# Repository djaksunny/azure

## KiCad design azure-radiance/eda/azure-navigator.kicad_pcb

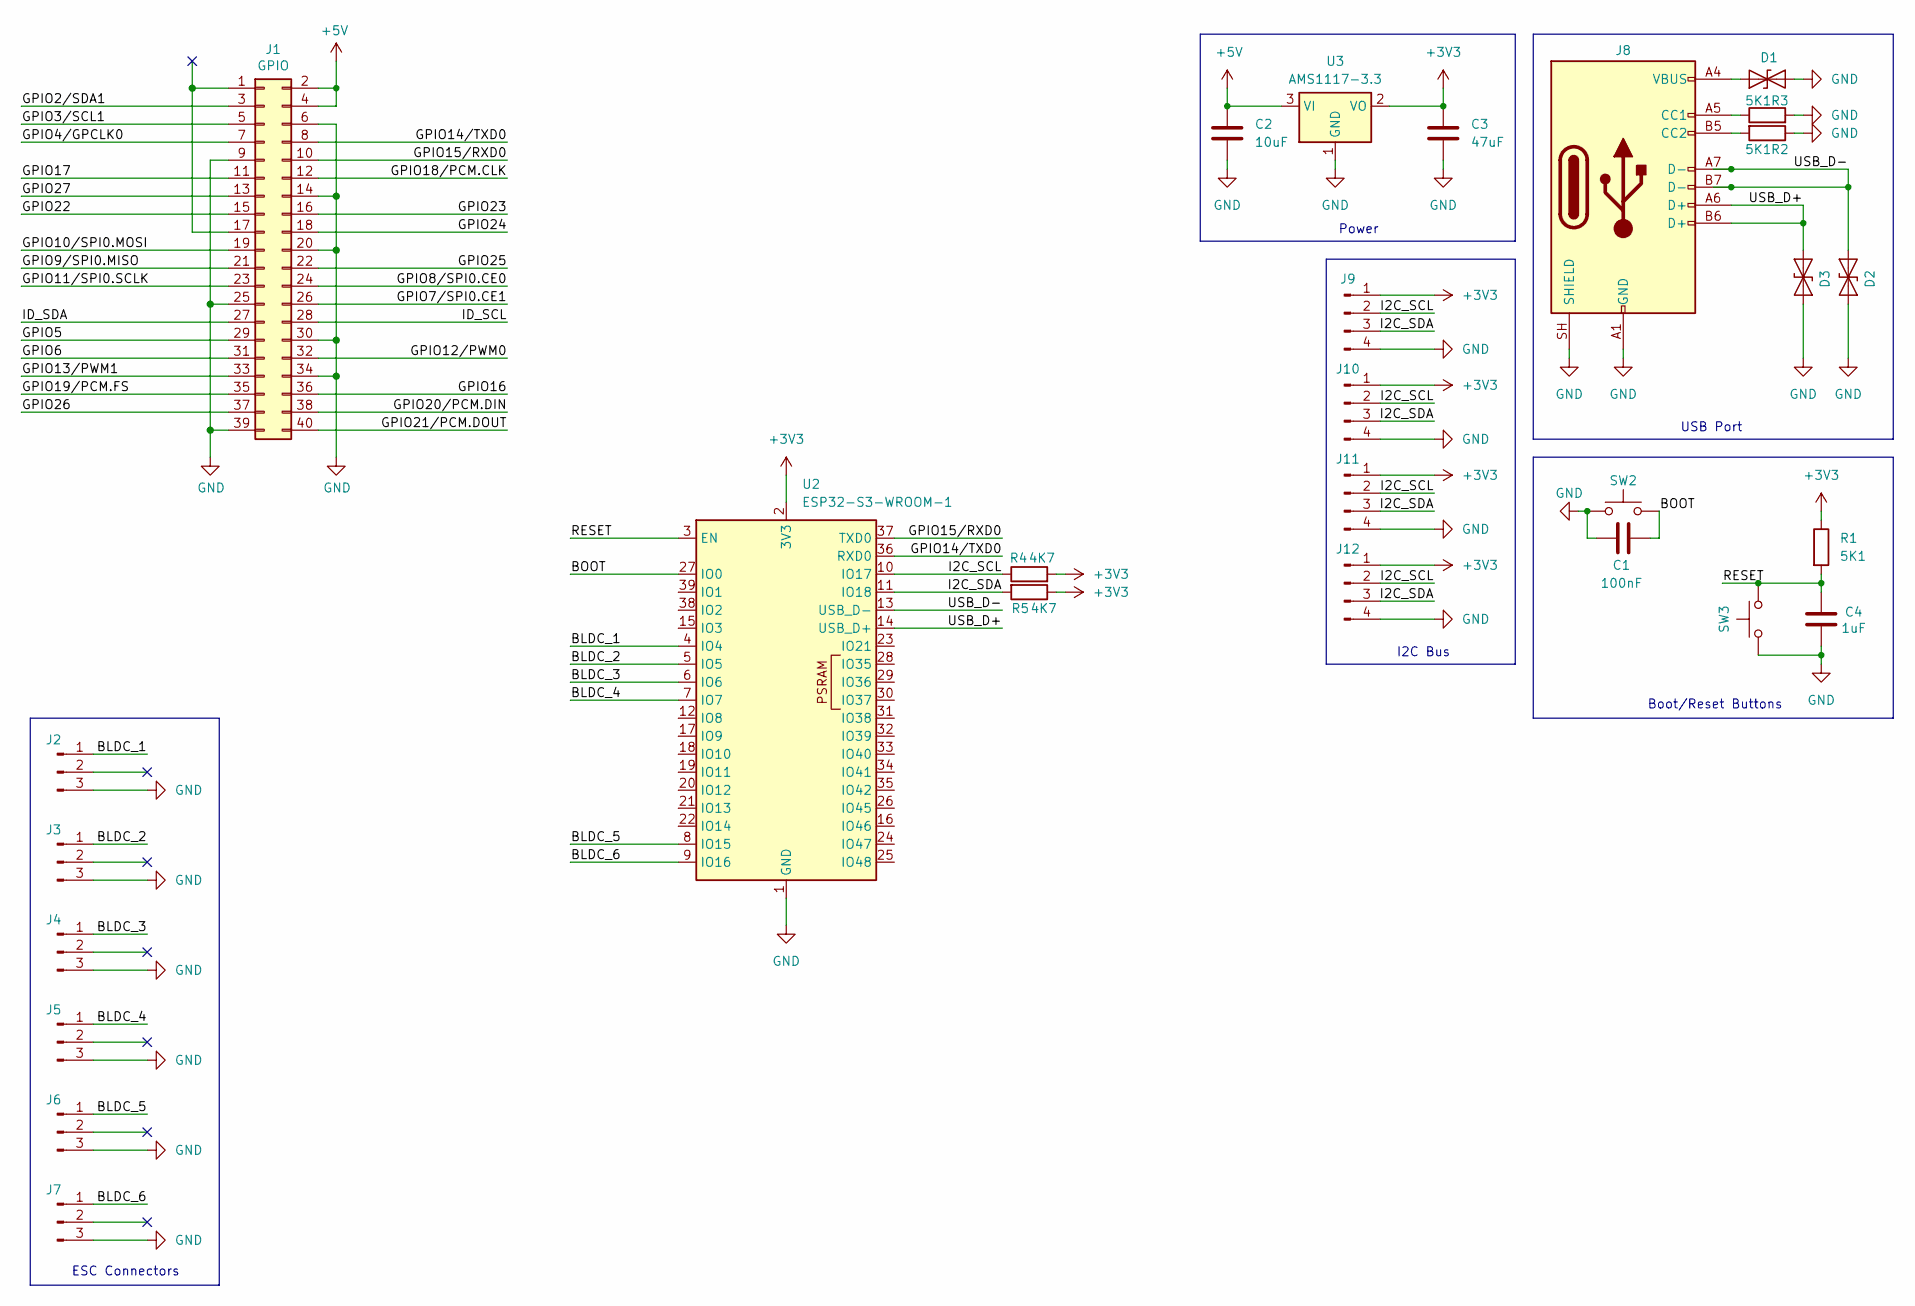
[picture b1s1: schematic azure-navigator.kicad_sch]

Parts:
C1: 100nF; C_1206_3216Metric
C2: 10uF; C_1206_3216Metric
C3: 47uF; C_1206_3216Metric
C4: 1uF; C_1206_3216Metric
D1, D3: ESD9B5.0ST5G; D_1206_3216Metric
D2: ESD9B5.0ST5G; D_SOD-923
J1: GPIO; PinSocket_2x20_P2.54mm_Vertical
J2, J3, J4, J5, J6, J7: Conn_01x03_Pin; JST_XH_B3B-XH-AM_1x03_P2.50mm_Vertical
J8: USB_C_Receptacle_USB2.0_14P; USB_C_Receptacle_Amphenol_124019772112A
J9, J10, J11, J12: Conn_01x04_Pin; JST_PH_B4B-PH-SM4-TB_1x04-1MP_P2.00mm_Vertical
R1, R2, R3: 5K1; R_1206_3216Metric
R4, R5: 4K7; R_1206_3216Metric
SW2, SW3: SW_Push; SW_SPST_PTS810
U2: ESP32-S3-WROOM-1
U3: AMS1117-3.3; SOT-223-3_TabPin2

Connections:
+3V3: C3.1, J9.1, J10.1, J11.1, J12.1, R1.1, R4.2, R5.1, U2.2 (3V3), U3.2 (VO)
+5V: C2.2, J1.2, J1.4, U3.3 (VI)
/BLDC_1: J2.1, U2.4 (IO4)
/BLDC_2: J3.1, U2.5 (IO5)
/BLDC_3: J4.1, U2.6 (IO6)
/BLDC_4: J5.1, U2.7 (IO7)
/BLDC_5: J6.1, U2.8 (IO15)
/BLDC_6: J7.1, U2.9 (IO16)
/BOOT: C1.1, SW2.2, U2.27 (IO0)
/GPIO2/SDA1: J1.3
/GPIO3/SCL1: J1.5
/GPIO4/GPCLK0: J1.7
/GPIO5: J1.29
/GPIO6: J1.31
/GPIO7/SPI0.CE1: J1.26
/GPIO8/SPI0.CE0: J1.24
/GPIO9/SPI0.MISO: J1.21
/GPIO10/SPI0.MOSI: J1.19
/GPIO11/SPI0.SCLK: J1.23
/GPIO12/PWM0: J1.32
/GPIO13/PWM1: J1.33
/GPIO14/TXD0: J1.8, U2.36 (RXD0)
/GPIO15/RXD0: J1.10, U2.37 (TXD0)
/GPIO16: J1.36
/GPIO17: J1.11
/GPIO18/PCM.CLK: J1.12
/GPIO19/PCM.FS: J1.35
/GPIO20/PCM.DIN: J1.38
/GPIO21/PCM.DOUT: J1.40
/GPIO22: J1.15
/GPIO23: J1.16
/GPIO24: J1.18
/GPIO25: J1.22
/GPIO26: J1.37
/GPIO27: J1.13
/I2C_SCL: J9.2, J10.2, J11.2, J12.2, R4.1, U2.10 (IO17)
/I2C_SDA: J9.3, J10.3, J11.3, J12.3, R5.2, U2.11 (IO18)
/ID_SCL: J1.28
/ID_SDA: J1.27
/RESET: C4.2, R1.2, SW3.2, U2.3 (EN)
/USB_D+: D3.1 (A1), J8.A6 (D+), J8.B6 (D+), U2.14 (USB_D+)
/USB_D-: D2.1 (A1), J8.A7 (D-), J8.B7 (D-), U2.13 (USB_D-)
GND: C1.2, C2.1, C3.2, C4.1, D1.2 (A2), D2.2 (A2), D3.2 (A2), J1.6, J1.9, J1.14, J1.20, J1.25, J1.30, J1.34, J1.39, J2.3, J3.3, J4.3, J5.3, J6.3, J7.3, J8.A1 (GND), J8.A12 (GND), J8.B1 (GND), J8.B12 (GND), J8.SH (SHIELD), J9.4, J10.4, J11.4, J12.4, R2.1, R3.2, SW2.1, SW3.1, U2.1 (GND), U2.40 (GND), U2.41 (GND), U3.1 (GND)
unnamed: D1.1 (A1), J8.A4 (VBUS), J8.A9 (VBUS), J8.B4 (VBUS), J8.B9 (VBUS)
unnamed: J8.A5 (CC1), R3.1
unnamed: J8.B5 (CC2), R2.2

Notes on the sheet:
USB Port
ESC Connectors
Power
I2C Bus
Boot/Reset Buttons

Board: 2 copper layers, 32 parts (1 on the bottom side), 20 nets, no tracks yet.

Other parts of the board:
MH1, MH2, MH3, MH4: MountingHole_2.7mm_M2.5
